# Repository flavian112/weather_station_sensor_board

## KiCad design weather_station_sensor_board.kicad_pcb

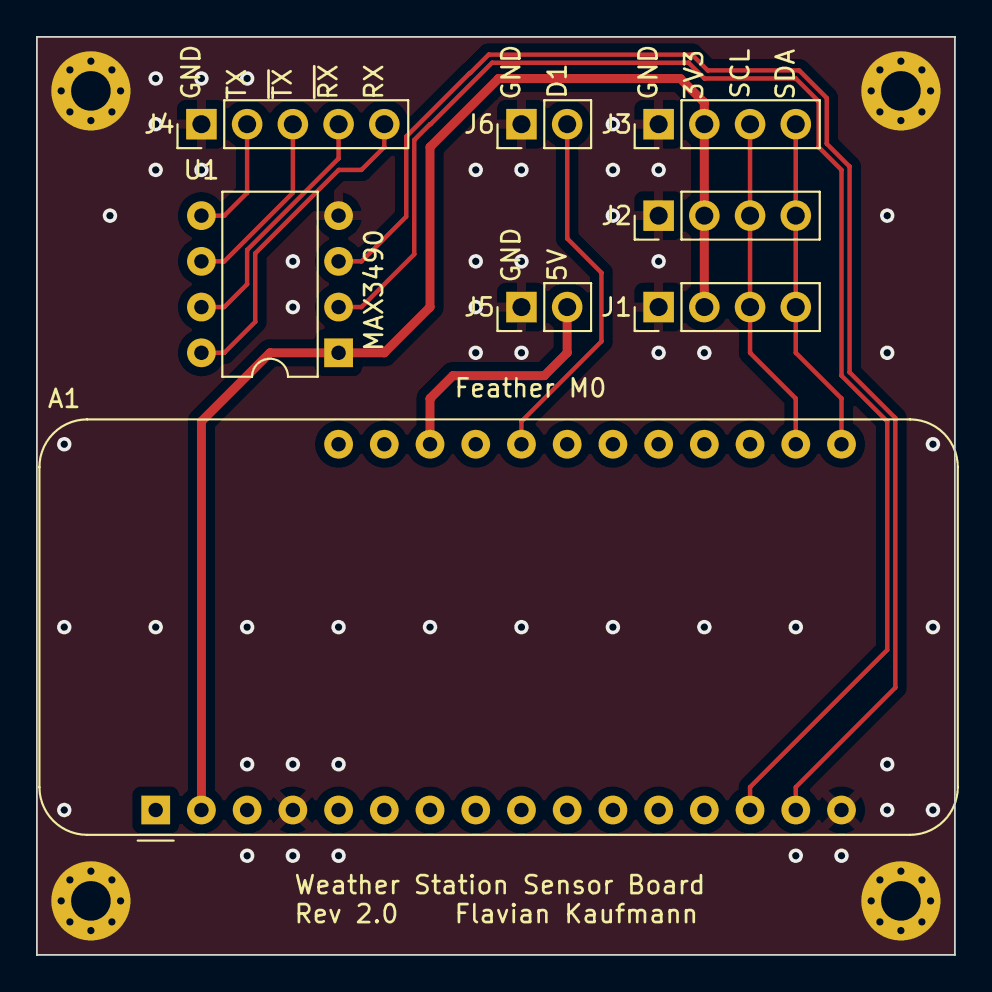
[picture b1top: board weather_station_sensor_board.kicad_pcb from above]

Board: 2 copper layers, 51.0 x 51.0 mm, 12 parts (0 on the bottom side), 12 nets.

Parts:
A1: Adafruit_Feather_M0_Basic_Proto; Adafruit_Feather
J1, J2, J3: Conn_01x04; PinHeader_1x04_P2.54mm_Vertical
J4: Conn_01x05; PinHeader_1x05_P2.54mm_Vertical
J5, J6: Conn_01x02; PinHeader_1x02_P2.54mm_Vertical
M1, M2, M3, M4: MountingHole_2.2mm_M2_Pad_Via
U1: MAX3490xPA; DIP-8_W7.62mm

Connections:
+3V3: A1.2 (3V3), J1.2, J2.2, J3.2, U1.1 (VCC)
+5V: A1.26 (USB), J5.2
D1: A1.24 (D12), J6.2
GND: A1.4 (GND), A1.16 (GND), J1.1, J2.1, J3.1, J4.1, J5.1, J6.1, M1.1, M2.1, M3.1, M4.1, U1.4 (GND)
RX: A1.14 (RX/D0), U1.2 (RO)
RX_NEG: J4.4, U1.7 (B)
RX_POS: J4.5, U1.8 (A)
SCL: A1.18 (SCL/D21), J1.3, J2.3, J3.3
SDA: A1.17 (SDA/D20), J1.4, J2.4, J3.4
TX: A1.15 (TX/D1), U1.3 (DI)
TX_NEG: J4.3, U1.6 (Z)
TX_POS: J4.2, U1.5 (Y)

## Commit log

2024-01-31 Initialized Project - designed board version REV1.0
2024-01-31 Added silscreen annotation for headers
2024-01-31 Added measurements
2024-01-31 rev 2.0
